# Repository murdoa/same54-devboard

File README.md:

# SAM-E54 Development Board
### Summary 
Development Board based around the Atmel SAME54 MCU exposing peripherals such as USB Host/Device, USB Serial, 100BASE-T Ethernet, SDHC and a QSPI with 1Gb flash.
### Features
- USB Host / Device
- USB Serial (CP2102) 
- SDHC Interface
- 100BASE-T Ethernet (KSZ8091RNA PHY)
- QSPI with W25N01GV footprint (1Gb flash)
- Cortex M ISP header
- 4 Indicator LEDs
- 3 Push Button switches
- 43 Pins accessible through 60 pin header

## Finished Board

## PCB Stackup
| Layer | Material | Thickness |
|:-----:|:--------:|:---------:|
| 1 | Copper | 0.035mm |
|  | Prepreg | 0.2mm |
| 2 | Copper | 0.0175mm |
|  | Core | 0.265mm |
| 3 | Copper | 0.0175mm |
|  | Prepreg | 0.2mm |
| 4 | Copper | 0.035mm |

## Copper Layers
| Layer 1 | Layer 2 |
|:----:|:----:|
||  |

| Layer 3 | Layer 4 |
|:----:|:----:|
||  |

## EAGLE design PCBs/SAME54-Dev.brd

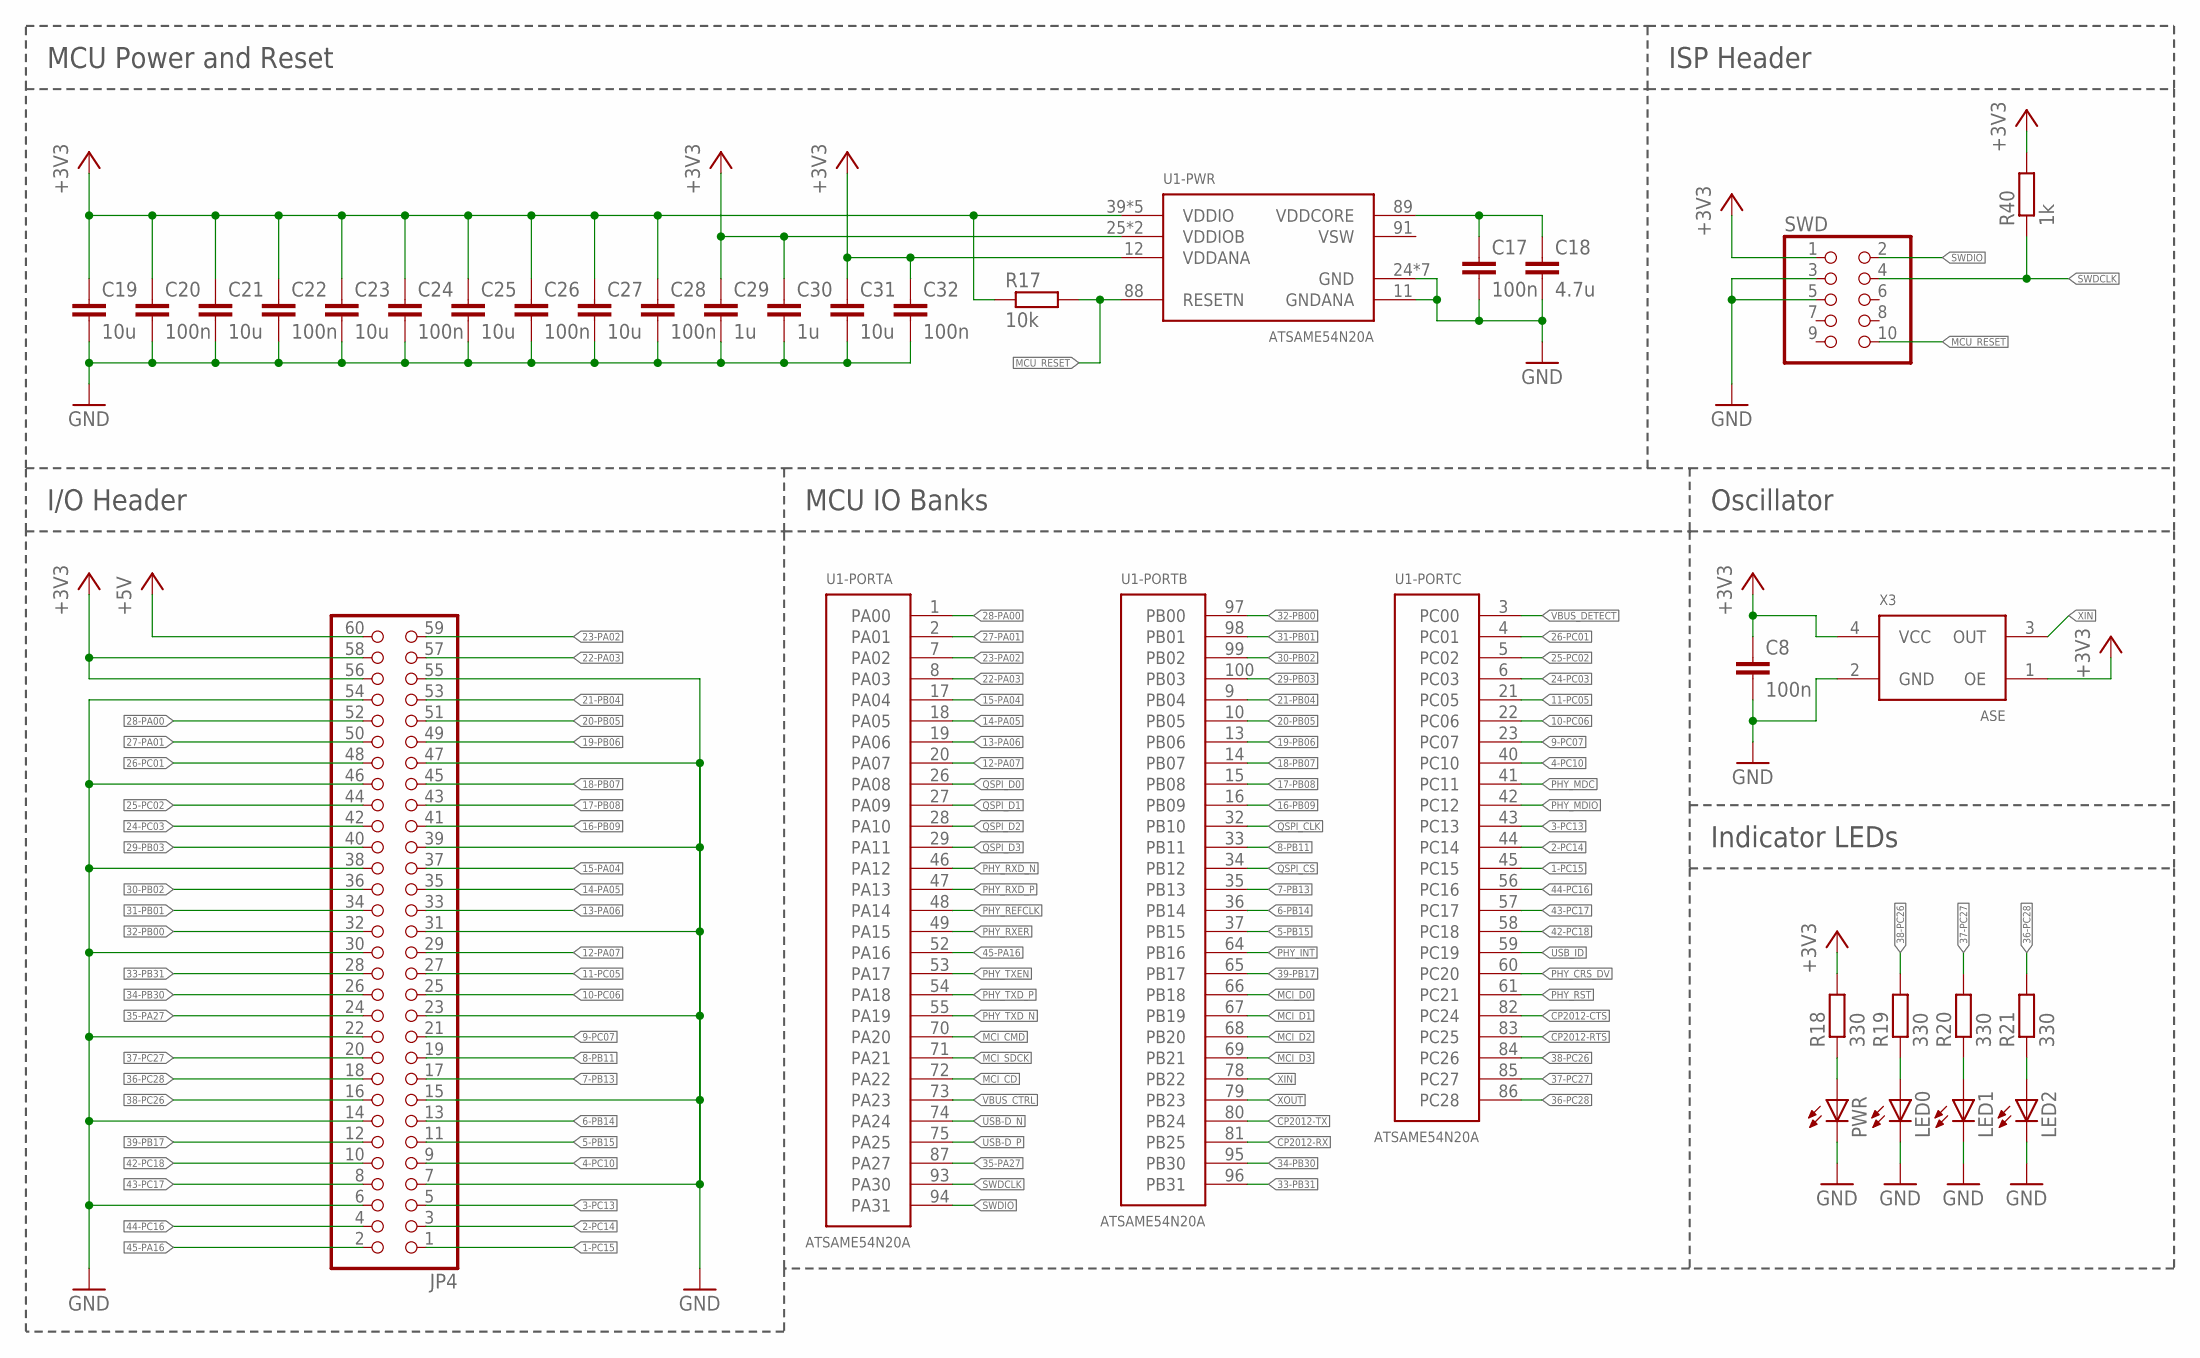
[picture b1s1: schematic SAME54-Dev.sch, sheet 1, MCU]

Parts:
C8, C17, C20, C22, C24, C26, C28, C32: 100n; C0603
C18: 4.7u; C0805
C19, C21, C23, C25, C27, C31: 10u; C0805
C29, C30: 1u; C0805
JP4: PINHD-2X30; 2X30
LED0, LED1, LED2: LEDCHIPLED_0603; CHIPLED_0603
PWR: LEDCHIPLED_0603; CHIPLED_0603
R17: 10k; R0603
R18, R19, R20, R21: 330; R0603
R40: 1k; R0603
SWD: PINHD-2X5; 2X05
U1: ATSAME54N20A; TQFP100
X3: ASE

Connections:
1-PC15: JP4.1, U1.45 (PC15)
2-PC14: JP4.3, U1.44 (PC14)
3-PC13: JP4.5, U1.43 (PC13)
4-PC10: JP4.9, U1.40 (PC10)
5-PB15: JP4.11, U1.37 (PB15)
6-PB14: JP4.13, U1.36 (PB14)
7-PB13: JP4.17, U1.35 (PB13)
8-PB11: JP4.19, U1.33 (PB11)
9-PC07: JP4.21, U1.23 (PC07)
10-PC06: JP4.25, U1.22 (PC06)
11-PC05: JP4.27, U1.21 (PC05)
12-PA07: JP4.29, U1.20 (PA07)
13-PA06: JP4.33, U1.19 (PA06)
14-PA05: JP4.35, U1.18 (PA05)
15-PA04: JP4.37, U1.17 (PA04)
16-PB09: JP4.41, U1.16 (PB09)
17-PB08: JP4.43, U1.15 (PB08)
18-PB07: JP4.45, U1.14 (PB07)
19-PB06: JP4.49, U1.13 (PB06)
20-PB05: JP4.51, U1.10 (PB05)
21-PB04: JP4.53, U1.9 (PB04)
22-PA03: JP4.57, U1.8 (PA03)
23-PA02: JP4.59, U1.7 (PA02)
24-PC03: JP4.42, U1.6 (PC03)
25-PC02: JP4.44, U1.5 (PC02)
26-PC01: JP4.48, U1.4 (PC01)
27-PA01: JP4.50, U1.2 (PA01)
28-PA00: JP4.52, U1.1 (PA00)
29-PB03: JP4.40, U1.100 (PB03)
30-PB02: JP4.36, U1.99 (PB02)
31-PB01: JP4.34, U1.98 (PB01)
32-PB00: JP4.32, U1.97 (PB00)
33-PB31: JP4.28, U1.96 (PB31); also elsewhere on the board
34-PB30: JP4.26, U1.95 (PB30); also elsewhere on the board
35-PA27: JP4.24, U1.87 (PA27); also elsewhere on the board
36-PC28: JP4.18, R21.2, U1.86 (PC28)
37-PC27: JP4.20, R20.2, U1.85 (PC27)
38-PC26: JP4.16, R19.2, U1.84 (PC26)
39-PB17: JP4.12, U1.65 (PB17)
42-PC18: JP4.10, U1.58 (PC18)
43-PC17: JP4.8, U1.57 (PC17)
44-PC16: JP4.4, U1.56 (PC16)
45-PA16: JP4.2, U1.52 (PA16)
+3V3: C8.1, C19.1, C20.1, C21.1, C22.1, C23.1, C24.1, C25.1, C26.1, C27.1, C28.1, C29.1, C30.1, C31.1, C32.1, JP4.56, JP4.58, R17.1, R18.2, R40.2, SWD.1, U1.12 (VDDANA), U1.25 (VDDIOB), U1.30 (VDDIOB), U1.39 (VDDIO), U1.51 (VDDIO), U1.63 (VDDIO), U1.77 (VDDIO), U1.92 (VDDIO), X3.1 (OE), X3.4 (VCC); also elsewhere on the board
+5V: JP4.60; also elsewhere on the board
CP2012-CTS: U1.82 (PC24); also elsewhere on the board
CP2012-RTS: U1.83 (PC25); also elsewhere on the board
CP2012-RX: U1.81 (PB25); also elsewhere on the board
CP2012-TX: U1.80 (PB24); also elsewhere on the board
GND: C8.2, C17.2, C18.2, C19.2, C20.2, C21.2, C22.2, C23.2, C24.2, C25.2, C26.2, C27.2, C28.2, C29.2, C30.2, C31.2, C32.2, JP4.6, JP4.7, JP4.14, JP4.15, JP4.22, JP4.23, JP4.30, JP4.31, JP4.38, JP4.39, JP4.46, JP4.47, JP4.54, JP4.55, LED0.C, LED1.C, LED2.C, PWR.C, SWD.3, SWD.5, U1.11 (GNDANA), U1.24 (GND), U1.31 (GND), U1.38 (GND), U1.50 (GND), U1.62 (GND), U1.76 (GND), U1.90 (GND), X3.2 (GND); also elsewhere on the board
MCI_CD: U1.72 (PA22); also elsewhere on the board
MCI_CMD: U1.70 (PA20); also elsewhere on the board
MCI_D0: U1.66 (PB18); also elsewhere on the board
MCI_D1: U1.67 (PB19); also elsewhere on the board
MCI_D2: U1.68 (PB20); also elsewhere on the board
MCI_D3: U1.69 (PB21); also elsewhere on the board
MCI_SDCK: U1.71 (PA21); also elsewhere on the board
MCU_RESET: R17.2, SWD.10, U1.88 (RESETN)
unnamed: PWR.A, R18.1
unnamed: LED0.A, R19.1
unnamed: C17.1, C18.1, U1.89 (VDDCORE)
unnamed: LED1.A, R20.1
unnamed: LED2.A, R21.1
PHY_CRS_DV: U1.60 (PC20); also elsewhere on the board
PHY_INT: U1.64 (PB16); also elsewhere on the board
PHY_MDC: U1.41 (PC11); also elsewhere on the board
PHY_MDIO: U1.42 (PC12); also elsewhere on the board
PHY_REFCLK: U1.48 (PA14); also elsewhere on the board
PHY_RST: U1.61 (PC21); also elsewhere on the board
PHY_RXD_N: U1.46 (PA12); also elsewhere on the board
PHY_RXD_P: U1.47 (PA13); also elsewhere on the board
PHY_RXER: U1.49 (PA15); also elsewhere on the board
PHY_TXD_N: U1.55 (PA19); also elsewhere on the board
PHY_TXD_P: U1.54 (PA18); also elsewhere on the board
PHY_TXEN: U1.53 (PA17); also elsewhere on the board
QSPI_CLK: U1.32 (PB10); also elsewhere on the board
QSPI_CS: U1.34 (PB12); also elsewhere on the board
QSPI_D0: U1.26 (PA08); also elsewhere on the board
QSPI_D1: U1.27 (PA09); also elsewhere on the board
QSPI_D2: U1.28 (PA10); also elsewhere on the board
QSPI_D3: U1.29 (PA11); also elsewhere on the board
SWDCLK: R40.1, SWD.4, U1.93 (PA30)
SWDIO: SWD.2, U1.94 (PA31)
USB-D_N: U1.74 (PA24); also elsewhere on the board
USB-D_P: U1.75 (PA25); also elsewhere on the board
USB_ID: U1.59 (PC19); also elsewhere on the board
VBUS_CTRL: U1.73 (PA23); also elsewhere on the board
VBUS_DETECT: U1.3 (PC00); also elsewhere on the board
XIN: U1.78 (PB22), X3.3 (OUT)
XOUT: U1.79 (PB23)

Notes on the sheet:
MCU Power and Reset
MCU IO Banks
I/O Header
ISP Header
Indicator LEDs
Oscillator

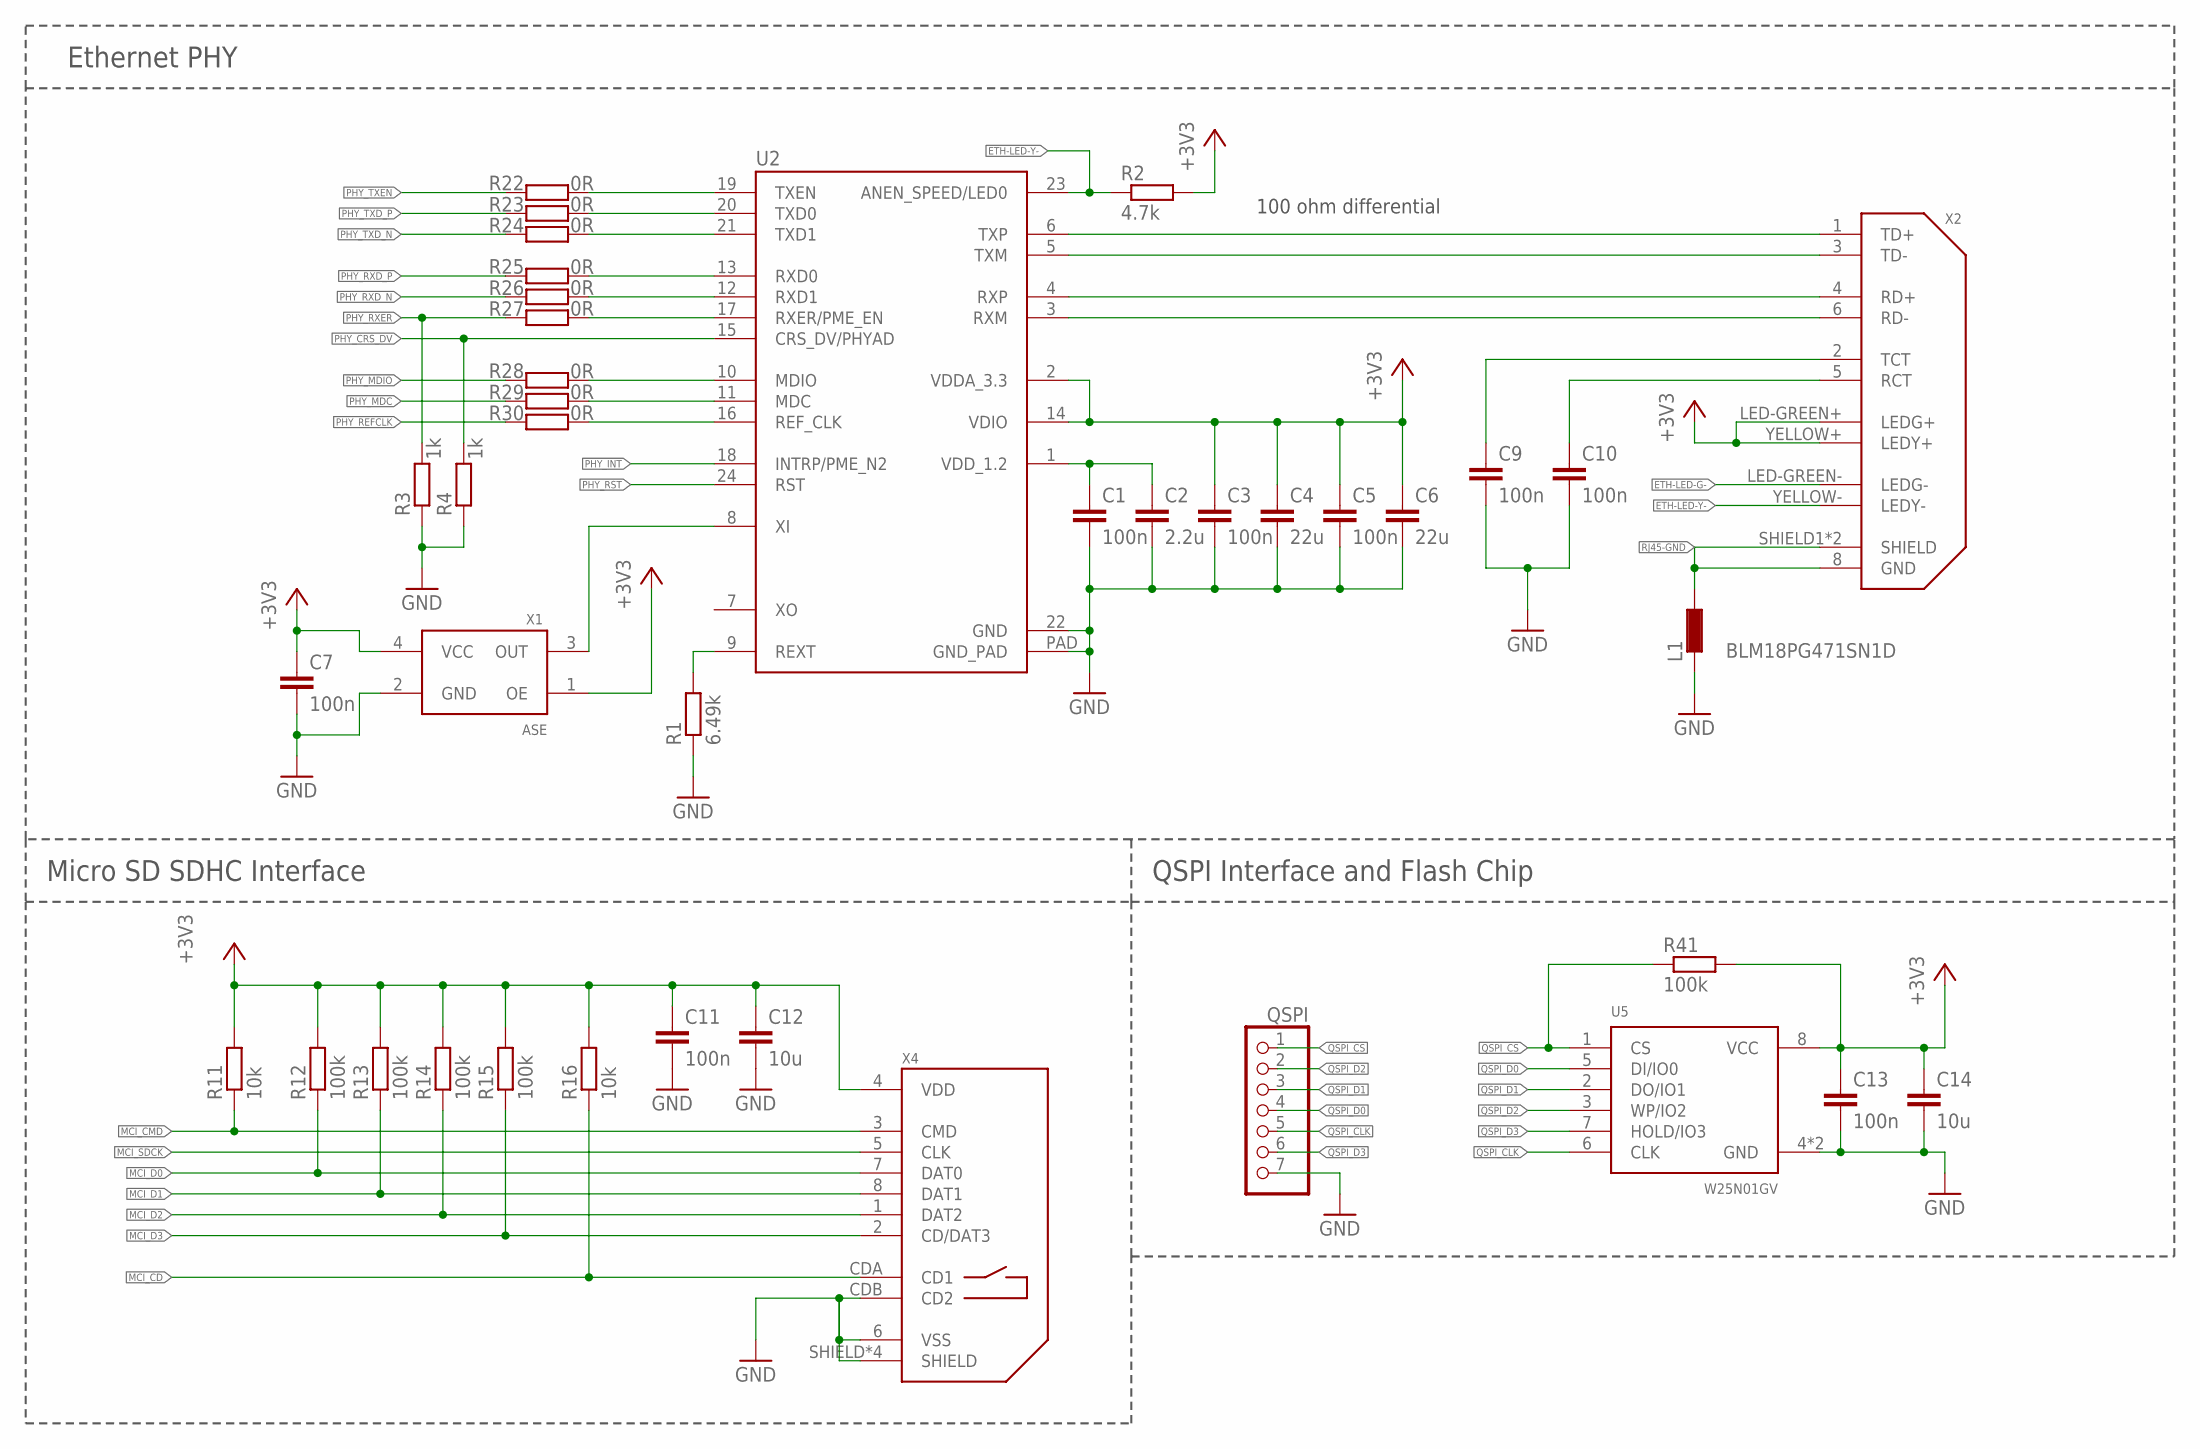
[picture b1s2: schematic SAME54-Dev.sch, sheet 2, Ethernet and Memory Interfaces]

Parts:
C1, C3, C5, C7, C9, C10, C11, C13: 100n; C0603
C2: 2.2u; C0805
C4, C6: 22u; C0805
C12, C14: 10u; C0805
L1: BLM18PG471SN1D; R0603
QSPI: PINHD-1X7; 1X07
R1: 6.49k; R0603
R2: 4.7k; R0603
R3, R4: 1k; R0603
R11, R16: 10k; R0603
R12, R13, R14, R15, R41: 100k; R0603
R22, R23, R24, R25, R26, R27, R28, R29, R30: 0R; R0603
U2: KSZ8091RNA; QFN24
U5: W25N01GV; WSON8
X1: ASE
X2: SI-50170-F
X4: DM3D-SF

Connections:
+3V3: C3.1, C4.1, C5.1, C6.1, C7.1, C11.1, C12.1, C13.1, C14.1, R2.2, R11.2, R12.2, R13.2, R14.2, R15.2, R16.2, R41.2, U2.2 (VDDA_3.3), U2.14 (VDIO), U5.8 (VCC), X1.1 (OE), X1.4 (VCC), X2.LED-GREEN+ (LEDG+), X2.YELLOW+ (LEDY+), X4.4 (VDD); also elsewhere on the board
ETH-LED-G-: X2.LED-GREEN- (LEDG-)
ETH-LED-Y-: R2.1, U2.23 (ANEN_SPEED/LED0), X2.YELLOW- (LEDY-)
GND: C1.2, C2.2, C3.2, C4.2, C5.2, C6.2, C7.2, C9.2, C10.2, C11.2, C12.2, C13.2, C14.2, L1.1, QSPI.7, R1.1, R3.1, R4.1, U2.22 (GND), U2.PAD (GND_PAD), U5.4 (GND), U5.PAD (GND), X1.2 (GND), X4.6 (VSS), X4.CDB (CD2), X4.SHIELD, X4.SHIELD1 (SHIELD), X4.SHIELD2 (SHIELD), X4.SHIELD3 (SHIELD); also elsewhere on the board
MCI_CD: R16.1, X4.CDA (CD1); also elsewhere on the board
MCI_CMD: R11.1, X4.3 (CMD); also elsewhere on the board
MCI_D0: R12.1, X4.7 (DAT0); also elsewhere on the board
MCI_D1: R13.1, X4.8 (DAT1); also elsewhere on the board
MCI_D2: R14.1, X4.1 (DAT2); also elsewhere on the board
MCI_D3: R15.1, X4.2 (CD/DAT3); also elsewhere on the board
MCI_SDCK: X4.5 (CLK); also elsewhere on the board
unnamed: U2.8 (XI), X1.3 (OUT)
unnamed: C9.1, X2.2 (TCT)
unnamed: C10.1, X2.5 (RCT)
unnamed: R1.2, U2.9 (REXT)
unnamed: C1.1, C2.1, U2.1 (VDD_1.2)
PHY_CRS_DV: R4.2, U2.15 (CRS_DV/PHYAD); also elsewhere on the board
PHY_INT: U2.18 (INTRP/PME_N2); also elsewhere on the board
PHY_MDC: R29.1; also elsewhere on the board
PHY_MDIO: R28.1; also elsewhere on the board
PHY_PIN_MDC: R29.2, U2.11 (MDC)
PHY_PIN_MDIO: R28.2, U2.10 (MDIO)
PHY_PIN_REFCLK: R30.2, U2.16 (REF_CLK)
PHY_PIN_RXD_N: R26.2, U2.12 (RXD1)
PHY_PIN_RXD_P: R25.2, U2.13 (RXD0)
PHY_PIN_RXER: R27.2, U2.17 (RXER/PME_EN)
PHY_PIN_TXD_N: R24.2, U2.21 (TXD1)
PHY_PIN_TXD_P: R23.2, U2.20 (TXD0)
PHY_PIN_TXEN: R22.2, U2.19 (TXEN)
PHY_REFCLK: R30.1; also elsewhere on the board
PHY_RST: U2.24 (RST); also elsewhere on the board
PHY_RXD_N: R26.1; also elsewhere on the board
PHY_RXD_P: R25.1; also elsewhere on the board
PHY_RXER: R3.2, R27.1; also elsewhere on the board
PHY_TXD_N: R24.1; also elsewhere on the board
PHY_TXD_P: R23.1; also elsewhere on the board
PHY_TXEN: R22.1; also elsewhere on the board
QSPI_CLK: QSPI.5, U5.6 (CLK); also elsewhere on the board
QSPI_CS: QSPI.1, R41.1, U5.1 (CS); also elsewhere on the board
QSPI_D0: QSPI.4, U5.5 (DI/IO0); also elsewhere on the board
QSPI_D1: QSPI.3, U5.2 (DO/IO1); also elsewhere on the board
QSPI_D2: QSPI.2, U5.3 (WP/IO2); also elsewhere on the board
QSPI_D3: QSPI.6, U5.7 (HOLD/IO3); also elsewhere on the board
RJ45-GND: L1.2, X2.8 (GND), X2.SHIELD1 (SHIELD), X2.SHIELD2 (SHIELD)
RX_N: U2.3 (RXM), X2.6 (RD-)
RX_P: U2.4 (RXP), X2.4 (RD+)
TX_N: U2.5 (TXM), X2.3 (TD-)
TX_P: U2.6 (TXP), X2.1 (TD+)

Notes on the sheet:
100 ohm differential
Ethernet PHY
Micro SD SDHC Interface
QSPI Interface and Flash Chip

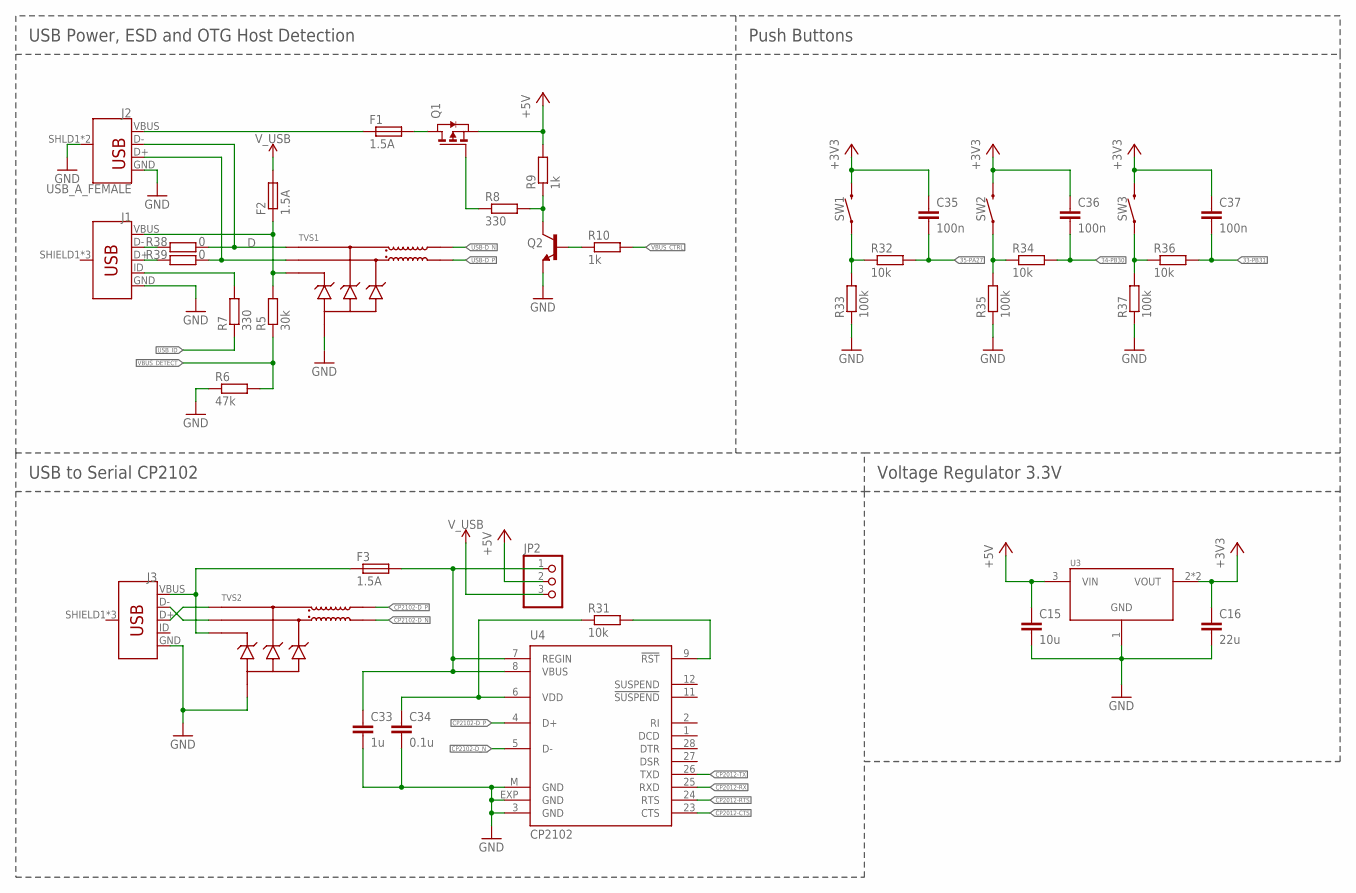
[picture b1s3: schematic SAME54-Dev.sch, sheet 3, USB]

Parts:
C15: 10u; C0805
C16: 22u; C0805
C33: 1u; C0805
C34: 0.1u; C0603
C35, C36, C37: 100n; C0603
F1, F2, F3: 1.5A; M1206
J1, J3: USB_MICRO-BREDUCED_PASTE; USB-B-MICRO-SMD_RED_PASTE
J2: USB_A_FEMALE; USB-A-S-SILK-FEMALE
JP2: PINHD-1X3; 1X03
Q1: PMOSSOT23; SOT-23
Q2: TRANS_NPN-MMBTA42; SOT23-3
R5: 30k; R0603
R6: 47k; R0603
R7, R8: 330; R0603
R9, R10: 1k; R0603
R31, R32, R34, R36: 10k; R0603
R33, R35, R37: 100k; R0603
R38, R39: 0; R0603
SW1, SW2, SW3: MOMENTARY-SWITCH-SPST-SMD-6.2MM-TALL; TACTILE_SWITCH_SMD_6.2MM_TALL
TVS1, TVS2: EMI2121MT; WDFN8
U3: AP1117; SOT223
U4: CP2102; MLP28

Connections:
33-PB31: C37.2, R36.2; also elsewhere on the board
34-PB30: C36.2, R34.2; also elsewhere on the board
35-PA27: C35.2, R32.2; also elsewhere on the board
+3V3: C16.1, C35.1, C36.1, C37.1, SW1.B2 (2), SW2.B2 (2), SW3.B2 (2), U3.2 (VOUT), U3.4 (VOUT); also elsewhere on the board
+5V: C15.1, JP2.2, Q1.2 (S), R9.2, U3.3 (VIN); also elsewhere on the board
CP2012-CTS: U4.23 (CTS); also elsewhere on the board
CP2012-RTS: U4.24 (RTS); also elsewhere on the board
CP2012-RX: U4.25 (RXD); also elsewhere on the board
CP2012-TX: U4.26 (TXD); also elsewhere on the board
CP2102-D_N: TVS2.7, U4.5 (D-)
CP2102-D_P: TVS2.8, U4.4 (D+)
D: J2.D-, R38.2, TVS1.1
D_P: J2.D+, R39.2, TVS1.2
GND: C15.2, C16.2, C33.2, C34.2, J1.GND, J2.GND, J2.SHLD1 (SHIELD), J2.SHLD2 (SHIELD), J3.GND, Q2.2 (E), R6.1, R33.1, R35.1, R37.1, TVS1.3 (3,4,5), TVS1.4 (3,4,5), TVS1.5 (3,4,5), TVS1.PAD (3,4,5), TVS2.3 (3,4,5), TVS2.4 (3,4,5), TVS2.5 (3,4,5), TVS2.PAD (3,4,5), U3.1 (GND), U4.3 (GND), U4.EXP (GND), U4.M (GND); also elsewhere on the board
unnamed: F1.1, J2.VBUS
unnamed: F1.2, Q1.1 (D)
unnamed: F2.1, J1.VBUS, R5.2, TVS1.6
unnamed: F3.1, J3.VBUS, TVS2.6
unnamed: C34.1, R31.1, U4.6 (VDD)
unnamed: C33.1, F3.2, JP2.1, U4.7 (REGIN), U4.8 (VBUS)
unnamed: Q1.3 (G), R8.1
unnamed: Q2.3 (C), R8.2, R9.1
unnamed: Q2.1 (B), R10.1
unnamed: R31.2, U4.9 (!RST)
unnamed: R32.1, R33.2, SW1.A2 (1)
unnamed: R34.1, R35.2, SW2.A2 (1)
unnamed: R36.1, R37.2, SW3.A2 (1)
PRE-TVS-D_N: J3.D-, TVS2.2
PRE-TVS-D_P: J3.D+, TVS2.1
USB-D_N: TVS1.8; also elsewhere on the board
USB-D_P: TVS1.7; also elsewhere on the board
USB_DEV_N: J1.D-, R38.1
USB_DEV_P: J1.D+, R39.1
USB_ID: R7.1; also elsewhere on the board
VBUS_CTRL: R10.2; also elsewhere on the board
VBUS_DETECT: R5.1, R6.2; also elsewhere on the board
VBUS_HOST_EN: J1.ID, R7.2
V_USB: F2.2, JP2.3

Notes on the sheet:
Push Buttons
USB Power, ESD and OTG Host Detection
USB to Serial CP2102
Voltage Regulator 3.3V

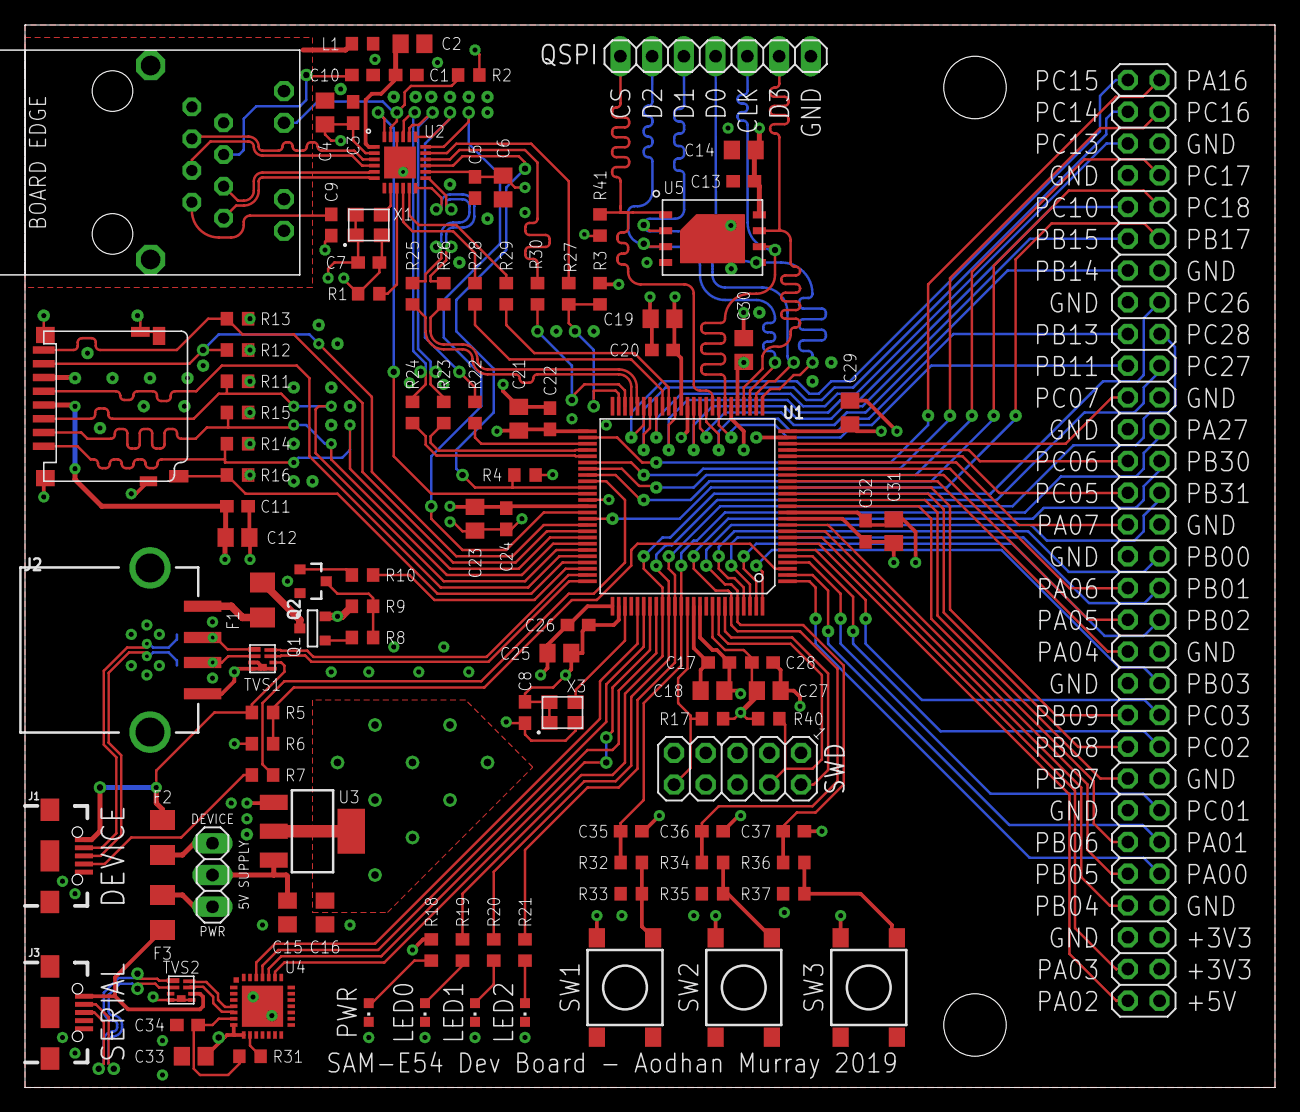
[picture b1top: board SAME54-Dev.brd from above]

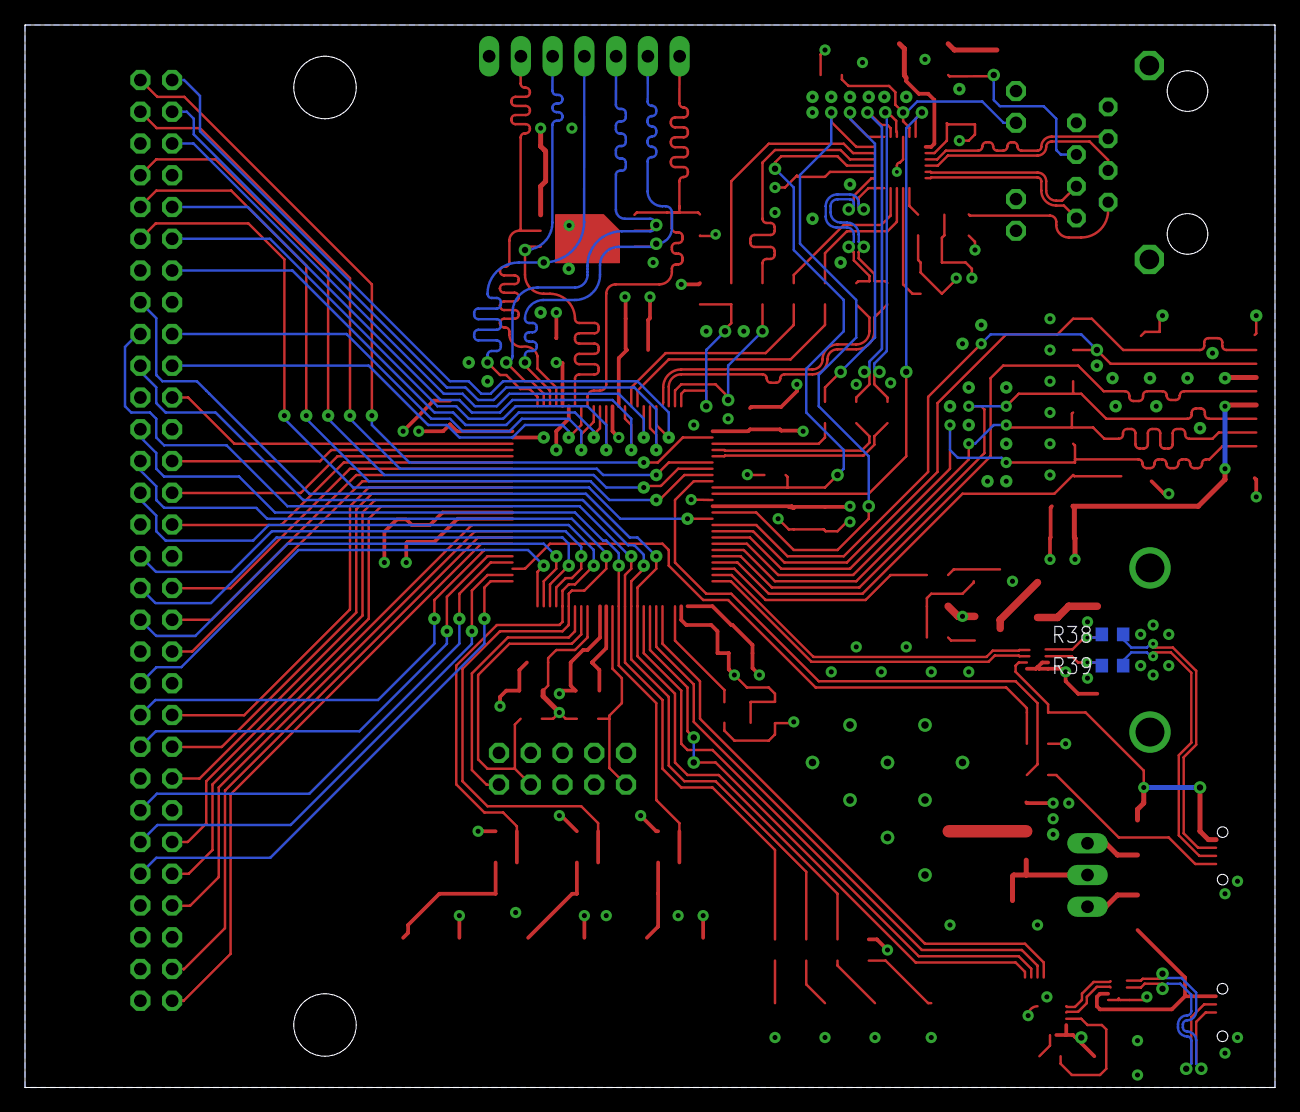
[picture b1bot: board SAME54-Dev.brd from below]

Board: 4 copper layers, 100.0 x 85.0 mm, 109 parts (2 on the bottom side), 132 nets.

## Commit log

2019-08-05 created repo
2019-11-25 Restructured project.
2019-11-25 Added images of copper layers and finished board
2019-11-25 README.md created
2019-11-25 README.md edited
2019-11-26 Added schematic PDF
2019-12-13 Renamed FinishedBoard.png to Final.png
2019-12-13 README.md edited online with Bitbucket
2020-01-02 Added Blog.md
2020-01-02 Edited markdown files

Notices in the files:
parts and their libraries:
SparkFun-Connectors: Licensing: Creative Commons ShareAlike 4.0 International - https://creativecommons.org/licenses/by-sa/4.0
